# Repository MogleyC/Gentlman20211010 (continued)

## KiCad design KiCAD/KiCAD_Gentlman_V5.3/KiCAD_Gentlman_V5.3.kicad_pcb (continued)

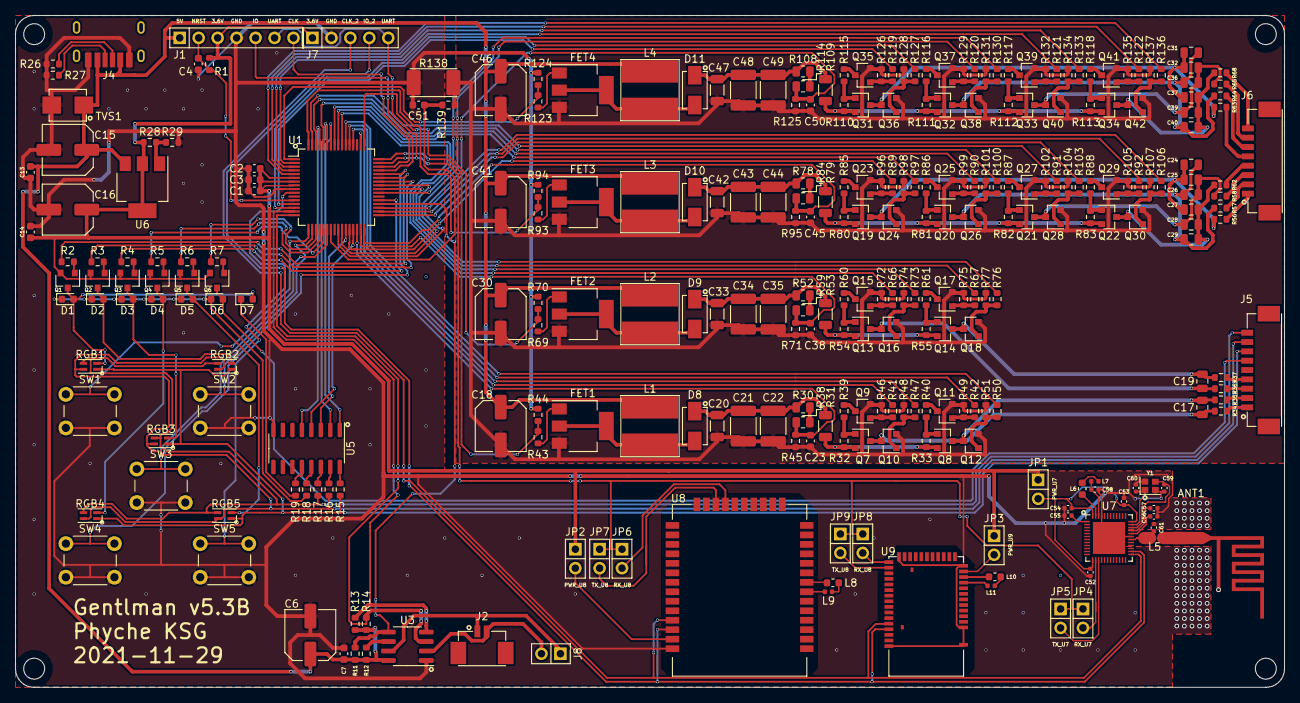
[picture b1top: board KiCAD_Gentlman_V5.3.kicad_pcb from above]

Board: 2 copper layers, 170.0 x 90.0 mm, 289 parts (0 on the bottom side), 207 nets.

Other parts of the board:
J1: PinHeader2.54mm_7; PinHeader_1x07_P2.54mm_Vertical
J2: 12505WR-02

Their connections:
+3.6V: J1.3; also elsewhere on the board
+5V: J1.1; also elsewhere on the board
/Main/NRST: J1.2; also elsewhere on the board
/Main/SWCLK: J1.7; also elsewhere on the board
/Main/SWDIO: J1.5; also elsewhere on the board
GNDPWR: J1.4; also elsewhere on the board
unnamed 80: J2.1; also elsewhere on the board
unnamed 81: J2.2; also elsewhere on the board
UART: J1.6; also elsewhere on the board

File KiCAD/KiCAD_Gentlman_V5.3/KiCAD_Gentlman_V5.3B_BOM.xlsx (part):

Reference | Quantity | Value | Footprint | Datasheet | Comment | Description | Field4 | MAKER | TYPE | Field5 | PartName | Shop
ANT1 | 1 | ANT | Custom:ANT_PATTERN | .\Dataseets\001-91445_AN91445_Antenna_Design_and_RF_Layout_Guidelines.pdf |  |  | PATTERN
C17 C19 C24 C25 C26 C27 C28 C29 C31 C32 C36 C37 C39 C40 | 14 | CAP_101K_250V_2012 | Custom:C_0805_2012Metric | ~ | CC0805JRNPOYBN101 | CHIP CERAMIC CAP | 101K/250V | YAGEO | 2012 |  |  | https://www.eleparts.co.kr/goods/view?no=9594793
C20 C33 C42 C47 | 4 | CAP_103K_250V_3216 | Custom:C_1206_3216Metric | .\Dataseets\TCC1206X7R103K251DT_10nF_250V_K.pdf | TCC1206X7R103K251DT | CHIP CERAMIC CAP | TCC1206X7R103K251DT | CCTC | 3216 |  |  | https://www.eleparts.co.kr/goods/view?no=8016042
C21 C22 C34 C35 C43 C44 C48 C49 | 8 | CAP_105K_250V_4532 | Custom:C_1812_4532Metric | .\Dataseets\FS43X105K251EGG_1uF_250V_K.pdf | FS43X105K251EGG | CHIP CERAMIC CAP | FS43X105K251EGG | WALSIN | 4532 |  |  | https://www.eleparts.co.kr/goods/view?no=8016951
C23 C38 C45 C50 C51 | 5 | CAP_103K_25V_1608 | Custom:C_0603_1608Metric | ~ | CC0603KRX7R8BB103 | CHIP CERAMIC CAP | 103K/25V | YAGEO | 1608 |  |  | https://www.eleparts.co.kr/goods/view?no=8057789#goodContent_3
C1 C2 C3 C4 C7 C13 C14 | 7 | CAP_104Z_25V_1608 | Custom:C_0603_1608Metric | ~ | CL10B104KA8NNNC | CHIP CERAMIC CAP | 104Z/25V | SAMSUNG ELECTRO-MECHANICS | 1608 |  |  | https://www.eleparts.co.kr/goods/view?no=8010066
C54 | 1 | CAP_4.7uF_1005 | Custom:C_0402_1005Metric | .\Dataseets\MLCC-1837944.pdf | CL05A475KP5NRNC | CHIP CERAMIC CAP | 4.7uF/짹10 | SAMSUNG ELECTRO-MECHANICS | 1005 |  | CL05A475KQ5NRNC | https://www.eleparts.co.kr/goods/view?no=8057798
C56 | 1 | CAP_N.C_1005 | Custom:C_0402_1005Metric | ~ | N.C | CHIP CERAMIC CAP | N.C | MURATA ELECTRONICS | 1005
C52 C53 C55 C57 | 4 | CAP_100nF_1005 | Custom:C_0402_1005Metric | .\Dataseets\GRM155R61H104KE14_01A-1983917.pdf | CL05A104KA5NNNC | CHIP CERAMIC CAP | 100nF/짹10 | SAMSUNG ELECTRO-MECHANICS | 1005 |  | GRM155R61H104KE14D | https://www.eleparts.co.kr/goods/view?no=8011439
C58 | 1 | CAP_1uF_1005 | Custom:C_0402_1005Metric | .\Dataseets\Samsung_MLCC_1837944-1929650.pdf | CL05A105KA5NQNC | CHIP CERAMIC CAP | 1uF/짹10 | SAMSUNG ELECTRO-MECHANICS | 1005 |  | CL05A105KP5NNWC | https://www.eleparts.co.kr/goods/view?no=8010445
C6 C15 C16 C18 C30 C41 C46 | 7 | CAP_220uF_6.3V_SC6.3X5.8 | Custom:C_Elec_6.3x5.8 | ~ | 220uF/6.3V | SMD ELECT CAPACITOR | 220uF/6.3V | SAMYOUNG | SC 6.3X5.8 | SC 6.3X5.8 |  | https://www.eleparts.co.kr/goods/view?no=3369557
C59 C60 | 2 | CAP_12pF_1005 | Custom:C_0402_1005Metric | .\Dataseets\GRM1555C1H120GA01_01A-1982688.pdf | 0402N120G250CT | CHIP CERAMIC CAP | 12pF/NP0/짹2 | WALSIN | 1005 |  | GRM1555C1H120GA01D | https://www.eleparts.co.kr/goods/view?no=9226620
C61 | 1 | CAP_0.8pF_1005 | Custom:C_0402_1005Metric | .\Dataseets\GRM1555C1HR80WA01_01A-1983059.pdf | GRM1555C1HR80WA01D | CHIP CERAMIC CAP | 0.8pF/NP0/짹5 | MURATA ELECTRONICS | 1005 |  | GRM1555C1HR80WA01D | https://www.eleparts.co.kr/goods/view?no=9591919
D1 D2 D3 D4 D5 D6 D7 | 7 | WR106SR-W | Custom:LED_0603_1608Metric | .\Dataseets\WR106SR-W.pdf | WR106SR-W | CHIP LED RED |  | BRIGHT LED | 1608 |  |  | https://www.eleparts.co.kr/goods/view?no=8104608
D8 D9 D10 D11 | 4 | MBRAF3200T3G | Custom:D_SMA | .\Dataseets\MBRAF3200T3_D-2315037.pdf | SS1200-LTP | SMD DIODE SCHOTTKY |  | Micro Commercial | SMA |  |  | https://www.eleparts.co.kr/goods/view?no=1799117
FET1 FET2 FET3 FET4 | 4 | FDT86246L | Custom:SOT-223-3_TabPin2 | .\Dataseets\FDT86246L-D.pdf | FDT86246L | SMD MOSFET N-CHANNEL |  | FAIRCHILD | SOT-223 |  |  | https://www.eleparts.co.kr/goods/view?no=6008399
J1 | 1 | PinHeader2.54mm_7 | Custom:PinHeader_1x07_P2.54mm_Vertical | ~ | PinHeader2.54mm-7P | PIN HEADER | DOWNLOAD | YEONHO ELECTRONICS | DIP-7
J2 | 1 | 12505WR-02 | Custom:12505WR-02 | .\Dataseets\12505-NN.pdf | 12505WR-02 | SMD WAFER | SPEAK1 | YEONHO ELECTRONICS | SMD-2 |  |  | https://www.devicemart.co.kr/goods/view?no=1381566
J4 | 1 | USB-TYPE-C-31-M-17 | Custom:TYPE-C-31-M-17-1 | .\Dataseets\Korean-Hroparts-Elec-TYPE-C-31-M-17.pdf | USB-TYPE-C-31-M-17 | SMD JACK USB C TYPE |  | Korean-Hroparts-Elec | SMD-6 |  |  | https://www.eleparts.co.kr/goods/view?no=7655653
J5 | 1 | 12505WS-09 | Custom:12505WS-09 | .\Dataseets\12505-NN.pdf | 12505WS-09 | SMD WAFER | CH1/CH2/RGB6 | YEONHO ELECTRONICS | SMD-9 |  |  | https://www.devicemart.co.kr/goods/view?no=12012614
J6 | 1 | 12505WS-08 | Custom:12505WS-08 | .\Dataseets\12505-NN.pdf | 12505WS-08 | SMD WAFER | CH3/CH4 | YEONHO ELECTRONICS | SMD-8 |  |  | https://www.devicemart.co.kr/goods/view?no=12012611
J7 | 1 | PinHeader2.54mm_5 | Custom:PinHeader_1x05_P2.54mm_Vertical | ~ | PinHeader2.54mm-5P | PIN HEADER |  |  | DIP-5
JP1 JP2 JP3 | 3 | PinHeader2.54mm-2-Jumper | Custom:PinHeader_1x02_P2.54mm_Vertical | ~ | PinHeader2.54mm-2P | PIN HEADER |  |  | DIP-2
L1 L2 L3 L4 | 4 | SC7850D-221K | Custom:L_SC7850D-221K | http://seokwangcoil.co.kr/7850 | SC7850D-221K | SMD INDUCTOR |  | SUHKWANG | 7850 |  |  | https://www.devicemart.co.kr/goods/view?no=6606
L5 | 1 | L_3.9nH | Custom:L_0402_1005Metric | .\Dataseets\7447840039G-2492425.pdf | LQG15HS3N9C02D | SMD INDUCTOR | 3.9nH/SHF6Ghz/짹5% | MURATA | 1005 |  | 7447840039G | https://www.eleparts.co.kr/goods/view?no=9578079
L6 L8 L10 | 3 | L_10uH | Custom:L_0603_1608Metric | .\Dataseets\JELF243B_0012-1633801.pdf | LQM18FN100M00D | SMD INDUCTOR | 10uH/50mA/짹20% | MURATA | 603 |  | LQM18FN100M00D | https://www.eleparts.co.kr/goods/view?no=7457243
L7 L9 L11 | 3 | L_15nH | Custom:L_0402_1005Metric | .\Dataseets\jti-cat-rf-ind-844822.pdf | LQG15HS15NJ02D | SMD INDUCTOR | 15nH/SHF2.45Ghz/짹10% | MURATA | 1005 |  | L-07C15NKV6T | https://www.eleparts.co.kr/goods/view?no=6591752
Q1 Q2 Q3 Q4 Q5 Q6 | 6 | MMBT200 | Custom:SOT-23 | .\Dataseets\AUKCS02423-1.pdf | MMBT200 | CHIP TRANSISTOR |  | ON SEMICONDUCTOR | SOT-23 |  |  | https://www.eleparts.co.kr/goods/view?no=7467326
Q7 Q8 Q13 Q14 Q19 Q20 Q21 Q22 Q31 Q32 Q33 Q34 | 12 | 2N5401S | Custom:SOT-23 | .\Dataseets\2N5401S.pdf | 2N5401S | CHIP TRANSISTOR |  | FIRST SILICON | SOT-23 |  |  | https://www.eleparts.co.kr/goods/view?no=6561296
Q9 Q10 Q11 Q12 Q15 Q16 Q17 Q18 Q23 Q24 Q25 Q26 Q27 Q28 Q29 Q30 Q35 Q36 Q37 Q38 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 | 24 | 2N5551S | Custom:SOT-23 | .\Dataseets\2N5550_1S_Ver2.pdf | 2N5551S | CHIP TRANSISTOR |  | FIRST SILICON | SOT-23 |  |  | https://www.eleparts.co.kr/goods/view?no=6561301
R1 | 1 | R_10KJ | Custom:R_0603_1608Metric | ~ | 10KJ | CHIP RESISTOR | 10KJ | WALSIN, SAMSUNG | 1608
R11 R12 R13 R14 R41 R42 R47 R50 R66 R67 R73 R76 R89 R90 R91 R92 R97 R100 R103 R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 | 29 | R_1KF | Custom:R_0603_1608Metric | ~ | 1KF | CHIP RESISTOR | 1KF | WALSIN, SAMSUNG | 1608 |  |  | https://www.devicemart.co.kr/goods/view?no=6058
R138 | 1 | R_0RJ_6432 | Custom:R_3522_6432Metric | ~ | 0RJ | CHIP RESISTOR | 0RJ | WALSIN, SAMSUNG | 6432 |  |  | https://www.devicemart.co.kr/goods/view?no=1089663
R15 R16 R17 R18 R19 | 5 | R_47RJ | Custom:R_0603_1608Metric | ~ | 47RJ | CHIP RESISTOR | 47RJ | WALSIN, SAMSUNG | 1608
R2 R3 R4 R5 R6 R7 | 6 | R_390RJ | Custom:R_0603_1608Metric | ~ | 390RJ | CHIP RESISTOR | 390RJ | WALSIN, SAMSUNG | 1608
R26 R27 | 2 | R_4.7KF | Custom:R_0603_1608Metric | ~ | 4.7KF | CHIP RESISTOR | 4.7KF | WALSIN, SAMSUNG | 1608
R28 | 1 | R_270RF | Custom:R_0603_1608Metric | ~ | 270RF | CHIP RESISTOR | 270RF | WALSIN, SAMSUNG | 1608
R29 | 1 | R_510RF | Custom:R_0603_1608Metric | ~ | 510RF | CHIP RESISTOR | 510RF | WALSIN, SAMSUNG | 1608
R30 R38 R52 R59 R78 R84 R108 R114 | 8 | R_150KF_2012 | Custom:R_0805_2012Metric | ~ | 150KF | CHIP RESISTOR | 150KF | WALSIN, SAMSUNG | 2012
R31 R53 R79 R109 | 4 | R_120RJ_3216 | Custom:R_1206_3216Metric | ~ | 120RJ | CHIP RESISTOR | 120RJ | WALSIN, SAMSUNG | 3216
R34 R35 R36 R37 R56 R57 R58 R62 R63 R64 R65 R68 | 12 | R_2.7KF | Custom:R_0603_1608Metric | ~ | 2.7KF | CHIP RESISTOR | 2.7KF | WALSIN, SAMSUNG | 1608
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
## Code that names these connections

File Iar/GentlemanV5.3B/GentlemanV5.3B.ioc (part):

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Mcu.Name=STM32G070RBTx
Mcu.Package=LQFP64
Mcu.UserName=STM32G070RBTx
PA0.GPIOParameters=GPIO_PuPd,GPIO_Label
PA0.GPIO_Label=SW1
PA0.GPIO_PuPd=GPIO_PULLUP
PA0.Signal=GPIO_Input
PA1.GPIOParameters=GPIO_PuPd,GPIO_Label
PA1.GPIO_Label=SW2
PA1.GPIO_PuPd=GPIO_PULLUP
PA1.Signal=GPIO_Input
PA10.GPIOParameters=PinState,GPIO_PuPd,GPIO_Label,GPIO_ModeDefaultOutputPP
PA10.GPIO_Label=LED_TR2
PA10.GPIO_ModeDefaultOutputPP=GPIO_MODE_OUTPUT_OD
PA10.GPIO_PuPd=GPIO_PULLUP
PA10.PinState=GPIO_PIN_SET
PA10.Signal=GPIO_Output
PA11\ [PA9].GPIOParameters=PinState,GPIO_PuPd,GPIO_Label,GPIO_ModeDefaultOutputPP
PA11\ [PA9].GPIO_Label=LED_TR1
PA11\ [PA9].GPIO_ModeDefaultOutputPP=GPIO_MODE_OUTPUT_OD
PA11\ [PA9].GPIO_PuPd=GPIO_PULLUP
PA11\ [PA9].PinState=GPIO_PIN_SET
PA11\ [PA9].Signal=GPIO_Output
PA12\ [PA10].GPIOParameters=GPIO_PuPd,GPIO_Label
PA12\ [PA10].GPIO_Label=SW4
PA12\ [PA10].GPIO_PuPd=GPIO_PULLUP
PA12\ [PA10].Signal=GPIO_Input
PA13.Mode=Serial_Wire
PA13.Signal=SYS_SWDIO
PA14-BOOT0.Mode=Serial_Wire
PA14-BOOT0.Signal=SYS_SWCLK
PA15.GPIOParameters=GPIO_ModeDefaultPP,GPIO_PuPd,GPIO_Label
PA15.GPIO_Label=UART2
PA15.GPIO_ModeDefaultPP=GPIO_MODE_AF_OD
PA15.GPIO_PuPd=GPIO_PULLUP
PA15.Signal=USART2_RX
PA2.GPIOParameters=PinState,GPIO_PuPd,GPIO_Label,GPIO_ModeDefaultOutputPP
PA2.GPIO_Label=LED_TR6
PA2.GPIO_ModeDefaultOutputPP=GPIO_MODE_OUTPUT_OD
PA2.GPIO_PuPd=GPIO_PULLUP
PA2.PinState=GPIO_PIN_SET
PA2.Signal=GPIO_Output
PA3.GPIOParameters=PinState,GPIO_PuPd,GPIO_Label,GPIO_ModeDefaultOutputPP
PA3.GPIO_Label=LED_TR5
PA3.GPIO_ModeDefaultOutputPP=GPIO_MODE_OUTPUT_OD
PA3.GPIO_PuPd=GPIO_PULLUP
PA3.PinState=GPIO_PIN_SET
PA3.Signal=GPIO_Output
PA4.GPIOParameters=PinState,GPIO_PuPd,GPIO_Label,GPIO_ModeDefaultOutputPP
PA4.GPIO_Label=LED_TR4
PA4.GPIO_ModeDefaultOutputPP=GPIO_MODE_OUTPUT_OD
PA4.GPIO_PuPd=GPIO_PULLUP
PA4.PinState=GPIO_PIN_SET
PA4.Signal=GPIO_Output
PA5.GPIOParameters=GPIO_PuPd,GPIO_Label
PA5.GPIO_Label=SW3
PA5.GPIO_PuPd=GPIO_PULLUP
PA5.Signal=GPIO_Input
PA6.GPIOParameters=GPIO_Label
PA6.GPIO_Label=ADC_CURR
PA6.Mode=IN6
PA6.Signal=ADC1_IN6
PA7.GPIOParameters=GPIO_PuPd,GPIO_Label
PA7.GPIO_Label=SOUND2_IN
PA7.GPIO_PuPd=GPIO_PULLDOWN
PA7.Signal=GPIO_Output
PA8.GPIOParameters=GPIO_Speed,PinState,GPIO_PuPd,GPIO_Label,GPIO_ModeDefaultOutputPP
PA8.GPIO_Label=SOUND1_EN
PA8.GPIO_ModeDefaultOutputPP=GPIO_MODE_OUTPUT_OD
PA8.GPIO_PuPd=GPIO_PULLUP
PA8.GPIO_Speed=GPIO_SPEED_FREQ_LOW
PA8.PinState=GPIO_PIN_SET
PA8.Signal=GPIO_Output
PA9.GPIOParameters=PinState,GPIO_PuPd,GPIO_Label,GPIO_ModeDefaultOutputPP
PA9.GPIO_Label=LED_TR3
PA9.GPIO_ModeDefaultOutputPP=GPIO_MODE_OUTPUT_OD
PA9.GPIO_PuPd=GPIO_PULLUP
PA9.PinState=GPIO_PIN_SET
PA9.Signal=GPIO_Output
PB0.GPIOParameters=GPIO_PuPd,GPIO_Label
PB0.GPIO_Label=LED_DTR3
PB0.GPIO_PuPd=GPIO_PULLDOWN
PB0.Signal=GPIO_Output
PB1.GPIOParameters=GPIO_PuPd,GPIO_Label
PB1.GPIO_Label=CH3_1_1
PB1.GPIO_PuPd=GPIO_PULLDOWN
PB1.Signal=GPIO_Output
PB10.GPIOParameters=GPIO_Label
PB10.GPIO_Label=ADC_CH1
PB10.Mode=IN11
PB10.Signal=ADC1_IN11
PB11.GPIOParameters=GPIO_Label
PB11.GPIO_Label=ADC_CH2
PB11.Mode=IN15
PB11.Signal=ADC1_IN15
PB12.GPIOParameters=GPIO_Label
PB12.GPIO_Label=ADC_CH3
PB12.Mode=IN16
PB12.Signal=ADC1_IN16
PB13.GPIOParameters=GPIO_PuPd,GPIO_Label
PB13.GPIO_Label=CH3_3_2
PB13.GPIO_PuPd=GPIO_PULLDOWN
PB13.Signal=GPIO_Output
PB14.GPIOParameters=GPIO_PuPd,GPIO_Label
PB14.GPIO_Label=CH3_4_1
PB14.GPIO_PuPd=GPIO_PULLDOWN
PB14.Signal=GPIO_Output
PB15.GPIOParameters=GPIO_PuPd,GPIO_Label
PB15.GPIO_Label=CH3_4_2
PB15.GPIO_PuPd=GPIO_PULLDOWN
PB15.Signal=GPIO_Output
PB2.GPIOParameters=GPIO_PuPd,GPIO_Label
PB2.GPIO_Label=LED_DTR4
PB2.GPIO_PuPd=GPIO_PULLDOWN
PB2.Signal=GPIO_Output
PB3.GPIOParameters=GPIO_PuPd,GPIO_Label
PB3.GPIO_Label=CH3_1_2
PB3.GPIO_PuPd=GPIO_PULLDOWN
PB3.Signal=GPIO_Output
PB4.GPIOParameters=GPIO_PuPd,GPIO_Label
PB4.GPIO_Label=LED_DTR1
PB4.GPIO_PuPd=GPIO_PULLDOWN
PB4.Signal=GPIO_Output
PB5.GPIOParameters=GPIO_PuPd,GPIO_Label
PB5.GPIO_Label=LED_DTR2
PB5.GPIO_PuPd=GPIO_PULLDOWN
PB5.Signal=GPIO_Output
PB6.GPIOParameters=GPIO_PuPd,GPIO_Label
PB6.GPIO_Label=CH3_2_1
PB6.GPIO_PuPd=GPIO_PULLDOWN
PB6.Signal=GPIO_Output
PB7.GPIOParameters=GPIO_PuPd,GPIO_Label
PB7.GPIO_Label=LED_DTR5
PB7.GPIO_PuPd=GPIO_PULLDOWN
PB7.Signal=GPIO_Output
PB8.GPIOParameters=GPIO_PuPd,GPIO_Label
PB8.GPIO_Label=CH3_2_2
PB8.GPIO_PuPd=GPIO_PULLDOWN
PB8.Signal=GPIO_Output
PB9.GPIOParameters=GPIO_PuPd,GPIO_Label
PB9.GPIO_Label=CH3_3_1
PB9.GPIO_PuPd=GPIO_PULLDOWN
PB9.Signal=GPIO_Output
PC0.GPIOParameters=GPIO_PuPd,GPIO_Label
PC0.GPIO_Label=CH4_1_1
PC0.GPIO_PuPd=GPIO_PULLDOWN
PC0.Signal=GPIO_Output
PC1.GPIOParameters=GPIO_PuPd,GPIO_Label
PC1.GPIO_Label=CH4_1_2
PC1.GPIO_PuPd=GPIO_PULLDOWN
PC1.Signal=GPIO_Output
PC10.GPIOParameters=GPIO_Speed,GPIO_PuPd,GPIO_Label
PC10.GPIO_Label=CTL_CH3
PC10.GPIO_PuPd=GPIO_PULLDOWN
PC10.GPIO_Speed=GPIO_SPEED_FREQ_LOW
PC10.Signal=S_TIM1_CH3
PC11.GPIOParameters=GPIO_PuPd,GPIO_Label
PC11.GPIO_Label=CTL_CH4
PC11.GPIO_PuPd=GPIO_PULLDOWN
PC11.Signal=S_TIM1_CH4
PC12.GPIOParameters=GPIO_PuPd,GPIO_Label
PC12.GPIO_Label=CH4_3_1
PC12.GPIO_PuPd=GPIO_PULLDOWN
PC12.Signal=GPIO_Output
PC13.GPIOParameters=GPIO_PuPd,GPIO_Label
PC13.GPIO_Label=CH4_3_2
PC13.GPIO_PuPd=GPIO_PULLDOWN
PC13.Signal=GPIO_Output
PC14-OSC32_IN\ (PC14).GPIOParameters=GPIO_PuPd,GPIO_Label
PC14-OSC32_IN\ (PC14).GPIO_Label=CH4_4_1
PC14-OSC32_IN\ (PC14).GPIO_PuPd=GPIO_PULLDOWN
PC14-OSC32_IN\ (PC14).Signal=GPIO_Output
PC15-OSC32_OUT\ (PC15).GPIOParameters=GPIO_PuPd,GPIO_Label
PC15-OSC32_OUT\ (PC15).GPIO_Label=CH4_4_2
PC15-OSC32_OUT\ (PC15).GPIO_PuPd=GPIO_PULLDOWN
PC15-OSC32_OUT\ (PC15).Signal=GPIO_Output
PC2.GPIOParameters=GPIO_Speed,PinState,GPIO_PuPd,GPIO_Label,GPIO_ModeDefaultOutputPP
PC2.GPIO_Label=SOUND1_DATA
PC2.GPIO_ModeDefaultOutputPP=GPIO_MODE_OUTPUT_OD
PC2.GPIO_PuPd=GPIO_PULLUP
PC2.GPIO_Speed=GPIO_SPEED_FREQ_LOW
PC2.PinState=GPIO_PIN_RESET
PC2.Signal=GPIO_Output
PC3.GPIOParameters=GPIO_Speed,PinState,GPIO_PuPd,GPIO_Label,GPIO_ModeDefaultOutputPP
PC3.GPIO_Label=SOUND1_CLK
PC3.GPIO_ModeDefaultOutputPP=GPIO_MODE_OUTPUT_OD
PC3.GPIO_PuPd=GPIO_PULLUP
PC3.GPIO_Speed=GPIO_SPEED_FREQ_LOW
PC3.PinState=GPIO_PIN_SET
PC3.Signal=GPIO_Output
PC4.GPIOParameters=GPIO_Label
PC4.GPIO_Label=ADC_CH4
PC4.Mode=IN17
PC4.Signal=ADC1_IN17
PC5.GPIOParameters=GPIO_PuPd,GPIO_Label
PC5.GPIO_Label=CH4_2_1
PC5.GPIO_PuPd=GPIO_PULLDOWN
PC5.Signal=GPIO_Output
PC6.GPIOParameters=GPIO_PuPd,GPIO_Label
PC6.GPIO_Label=SOUND2_SD
PC6.GPIO_PuPd=GPIO_PULLDOWN
PC6.Signal=GPIO_Output
PC7.GPIOParameters=GPIO_PuPd,GPIO_Label
PC7.GPIO_Label=CH4_2_2
PC7.GPIO_PuPd=GPIO_PULLDOWN
PC7.Signal=GPIO_Output
PC8.GPIOParameters=GPIO_PuPd,GPIO_Label
PC8.GPIO_Label=CTL_CH1
PC8.GPIO_PuPd=GPIO_PULLDOWN
PC8.Signal=S_TIM1_CH1
PC9.GPIOParameters=GPIO_PuPd,GPIO_Label
PC9.GPIO_Label=CTL_CH2
PC9.GPIO_PuPd=GPIO_PULLDOWN
PC9.Signal=S_TIM1_CH2
PD0.GPIOParameters=GPIO_PuPd,GPIO_Label
PD0.GPIO_Label=CH1_1_1
PD0.GPIO_PuPd=GPIO_PULLDOWN
PD0.Signal=GPIO_Output
PD1.GPIOParameters=GPIO_PuPd,GPIO_Label
PD1.GPIO_Label=FLASH_CLK
PD1.GPIO_PuPd=GPIO_PULLDOWN
PD1.Signal=GPIO_Output
PD2.GPIOParameters=GPIO_PuPd,GPIO_Label
PD2.GPIO_Label=CH1_1_2
PD2.GPIO_PuPd=GPIO_PULLDOWN
PD2.Signal=GPIO_Output
PD3.GPIOParameters=GPIO_PuPd,GPIO_Label
PD3.GPIO_Label=CH1_2_1
PD3.GPIO_PuPd=GPIO_PULLDOWN
PD3.Signal=GPIO_Output
PD4.GPIOParameters=GPIO_PuPd,GPIO_Label
PD4.GPIO_Label=CH1_2_2
PD4.GPIO_PuPd=GPIO_PULLDOWN
PD4.Signal=GPIO_Output
PD5.GPIOParameters=GPIO_PuPd,GPIO_Label
PD5.GPIO_Label=CH2_1_1
PD5.GPIO_PuPd=GPIO_PULLDOWN
PD5.Signal=GPIO_Output
PD6.GPIOParameters=GPIO_PuPd,GPIO_Label
PD6.GPIO_Label=CH2_1_2
PD6.GPIO_PuPd=GPIO_PULLDOWN
PD6.Signal=GPIO_Output
PD8.GPIOParameters=GPIO_PuPd,GPIO_Label
PD8.GPIO_Label=CH2_2_1
PD8.GPIO_PuPd=GPIO_PULLDOWN
PD8.Signal=GPIO_Output
PD9.GPIOParameters=GPIO_PuPd,GPIO_Label
PD9.GPIO_Label=CH2_2_2
PD9.GPIO_PuPd=GPIO_PULLDOWN
PD9.Signal=GPIO_Output
PF0-OSC_IN\ (PF0).GPIOParameters=GPIO_PuPd,GPIO_Label
PF0-OSC_IN\ (PF0).GPIO_Label=SW5
PF0-OSC_IN\ (PF0).GPIO_PuPd=GPIO_PULLUP
PF0-OSC_IN\ (PF0).Signal=GPIO_Input
RCC.HSE_VALUE=8000000
RCC.SYSCLKFreq_VALUE=64000000
RCC.SYSCLKSource=RCC_SYSCLKSOURCE_PLLCLK
board=custom

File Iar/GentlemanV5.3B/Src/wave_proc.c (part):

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//#define CH4_CH4_1_Flag 0x80
//#define CH4_CH4_2_Flag 0x40

#define CH1_P1_CTL1	RunTblBuf.CH1H1
#define CH1_P1_CTL2	RunTblBuf.CH1L1
#define CH1_P2_CTL1	RunTblBuf.CH1H2
#define CH1_P2_CTL2	RunTblBuf.CH1L2

#define CH2_P1_CTL1	RunTblBuf.CH2H1
#define CH2_P1_CTL2	RunTblBuf.CH2L1
#define CH2_P2_CTL1	RunTblBuf.CH2H2
#define CH2_P2_CTL2	RunTblBuf.CH2L2

#define CH3_P1_CTL1	RunTblBuf.CH3H1
#define CH3_P1_CTL2	RunTblBuf.CH3L1
#define CH3_P2_CTL1	RunTblBuf.CH3H2
#define CH3_P2_CTL2	RunTblBuf.CH3L2
#define CH3_P3_CTL1	RunTblBuf.CH3H3
#define CH3_P3_CTL2	RunTblBuf.CH3L3
#define CH3_P4_CTL1	RunTblBuf.CH3H4
#define CH3_P4_CTL2	RunTblBuf.CH3L4

#define CH4_P1_CTL1	RunTblBuf.CH4H1
#define CH4_P1_CTL2	RunTblBuf.CH4L1
#define CH4_P2_CTL1	RunTblBuf.CH4H2
#define CH4_P2_CTL2	RunTblBuf.CH4L2
#define CH4_P3_CTL1	RunTblBuf.CH4H3
#define CH4_P3_CTL2	RunTblBuf.CH4L3
#define CH4_P4_CTL1	RunTblBuf.CH4H4
#define CH4_P4_CTL2	RunTblBuf.CH4L4

#define PT_Freq_Step_Change 10

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	case 1:
	{
		//Ch_1 Low & Discharge
		CH1_P1_CTL2 = 0;
		CH1_P2_CTL2 = 0;

		//Ch_1_1
		if (CH1_P1_CTL1 == 1)
		{
			CH1_P1_CTL1 = 0;
			CH1_P1_CTL2 = 1;
		}

		//Ch_1_2
		if (CH1_P2_CTL1 == 1)
		{
			CH1_P2_CTL1 = 0;
			CH1_P2_CTL2 = 1;
		}

		break;	//switch exit
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	case 2:
	{
		//Ch_2 Low & Discharge
		CH2_P1_CTL2 = 0;
		CH2_P2_CTL2 = 0;

		//Ch_1_1
		if (CH2_P1_CTL1 == 1)
		{
			CH2_P1_CTL1 = 0;
			CH2_P1_CTL2 = 1;
		}

		//Ch_1_2
		if (CH2_P2_CTL1 == 1)
		{
			CH2_P2_CTL1 = 0;
			CH2_P2_CTL2 = 1;
		}

		break;	//switch exit
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	case 3:
	{
		//Ch_3 Low & Discharge
		CH3_P1_CTL2 = 0;
		CH3_P2_CTL2 = 0;
		CH3_P3_CTL2 = 0;
		CH3_P4_CTL2 = 0;

		//Ch_3_1
		if (CH3_P1_CTL1 == 1)
		{
			CH3_P1_CTL1 = 0;
			CH3_P1_CTL2 = 1;
		}

		//Ch_3_2
		if (CH3_P2_CTL1 == 1)
		{
			CH3_P2_CTL1 = 0;
			CH3_P2_CTL2 = 1;
		}

		//Ch_3_3
		if (CH3_P3_CTL1 == 1)
		{
			CH3_P3_CTL1 = 0;
			CH3_P3_CTL2 = 1;
		}

		//Ch_3_4
		if (CH3_P4_CTL1 == 1)
		{
			CH3_P4_CTL1 = 0;
			CH3_P4_CTL2 = 1;
		}

		break;	//switch exit
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	case 4:
	{
		//Ch_4 Low & Discharge
		CH4_P1_CTL2 = 0;
		CH4_P2_CTL2 = 0;
		CH4_P3_CTL2 = 0;
		CH4_P4_CTL2 = 0;

		//Ch_4_1
		if (CH4_P1_CTL1 == 1)
		{
			CH4_P1_CTL1 = 0;
			CH4_P1_CTL2 = 1;
		}

		//Ch_4_2
		if (CH4_P2_CTL1 == 1)
		{
			CH4_P2_CTL1 = 0;
			CH4_P2_CTL2 = 1;
		}

		//Ch_4_3
		if (CH4_P3_CTL1 == 1)
		{
			CH4_P3_CTL1 = 0;
			CH4_P3_CTL2 = 1;
		}

		//Ch_4_4
		if (CH4_P4_CTL1 == 1)
		{
			CH4_P4_CTL1 = 0;
			CH4_P4_CTL2 = 1;
		}

		break;	//switch exit
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				tmpPinSetValue = Pattern_Base[PT_Freq_CategoryID[0]][PT_Freq_ID];
				if ((tmpPinSetValue & CH1_PD1_Flag) != 0x00)
				{
					CH1_P1_CTL1 = 1;
					CH1_P2_CTL2 = 1;
				}
				else if ((tmpPinSetValue & CH1_PD2_Flag) != 0x00)
				{
					CH1_P2_CTL1 = 1;
					CH1_P1_CTL2 = 1;
				}

				++PT_Freq_Step;
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				tmpPinSetValue = Pattern_Base[PT_Freq_CategoryID[1]][PT_Freq_ID];
				if ((tmpPinSetValue & CH2_PD1_Flag) != 0x00)
				{
					CH2_P1_CTL1 = 1;
					CH2_P2_CTL2 = 1;
				}
				else if ((tmpPinSetValue & CH2_PD2_Flag) != 0x00)
				{
					CH2_P2_CTL1 = 1;
					CH2_P1_CTL2 = 1;
				}

				++PT_Freq_Step;
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				//Ch_3_1
				if ((tmpPinSetValue & CH3_CH1_1_Flag) != 0x00)
				{
					CH3_P1_CTL1 = 1;
				}
				else if ((tmpPinSetValue & CH3_CH1_2_Flag) != 0x00)
				{
					CH3_P1_CTL2 = 1;
				}

				//Ch_3_2
				if ((tmpPinSetValue & CH3_CH2_1_Flag) != 0x00)
				{
					CH3_P2_CTL1 = 1;
				}
				else if ((tmpPinSetValue & CH3_CH2_2_Flag) != 0x00)
				{
					CH3_P2_CTL2 = 1;
				}

				//Ch_3_3
				if ((tmpPinSetValue & CH3_CH3_1_Flag) != 0x00)
				{
					CH3_P3_CTL1 = 1;
				}
				else if ((tmpPinSetValue & CH3_CH3_2_Flag) != 0x00)
				{
					CH3_P3_CTL2 = 1;
				}

				//Ch_3_4
				if ((tmpPinSetValue & CH3_CH4_1_Flag) != 0x00)
				{
					CH3_P4_CTL1 = 1;
				}
				else if ((tmpPinSetValue & CH3_CH4_2_Flag) != 0x00)
				{
					CH3_P4_CTL2 = 1;
				}

				++PT_Freq_Step;
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				//Ch_4_1
				if ((tmpPinSetValue & CH4_CH1_1_Flag) != 0x00)
				{
					CH4_P1_CTL1 = 1;
				}
				else if ((tmpPinSetValue & CH4_CH1_2_Flag) != 0x00)
				{
					CH4_P1_CTL2 = 1;
				}

				//Ch_4_2
				if ((tmpPinSetValue & CH4_CH2_1_Flag) != 0x00)
				{
					CH4_P2_CTL1 = 1;
				}
				else if ((tmpPinSetValue & CH4_CH2_2_Flag) != 0x00)
				{
					CH4_P2_CTL2 = 1;
				}

				//Ch_4_3
				if ((tmpPinSetValue & CH4_CH3_1_Flag) != 0x00)
				{
					CH4_P3_CTL1 = 1;
				}
				else if ((tmpPinSetValue & CH4_CH3_2_Flag) != 0x00)
				{
					CH4_P3_CTL2 = 1;
				}

				//Ch_4_4
				if ((tmpPinSetValue & CH4_CH4_1_Flag) != 0x00)
				{
					CH4_P4_CTL1 = 1;
				}
				else if ((tmpPinSetValue & CH4_CH4_2_Flag) != 0x00)
				{
					CH4_P4_CTL2 = 1;
				}

				++PT_Freq_Step;
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
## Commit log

2021-10-10 KSG : 라이선스 및 리드미 파일 제작
2021-10-10 KSG : KiCad프로젝트 생성 및 무시규칙, 유틸리티 업데이트
2021-10-18 KSG : 블루투스 모듈 데이터시트 업로드
2021-10-18 KSG : 잘못된 이름의 파일 제거
2021-10-18 KSG : KICAD 연습(G070RB 심볼 및 풋프린트 얹기)
2021-10-19 KSG : 일부파일 폴더 위치 변경
2021-10-19 KSG : KICAD 라이브러리 대량 업데이트 및 회로도 제작 연습
2021-10-20 KSG : 뉴클레오 UART 블루투스 통신 테스트 완료(휴대폰과 통신)
2021-10-28 KSG : 블루투스 모듈 오리지널 Hex파일 백업
2021-10-29 KSG : nRF5_SDK 업로드
2021-10-29 KSG : 커스텀 프로젝트 제작(GPIO, Dealy 구현 및 테스트)
2021-10-29 KSG : GPIOE 코드 구현
2021-10-29 KSG : doxy파일 구성 및 example ignore 구성
2021-10-29 KSG : Ses 셋팅 최적화 및 설정파일저장, 소스파일 최적화
2021-10-29 KSG : systick_delay적용 및 sdk_config wizard 설정
2021-10-30 KSG : 시스템틱 미싱코드 추가 및 클락 시스템 제어 코드 테스트
2021-10-30 KSG : 핀번호 관리 헤더 추가 및 LED 2개로 내용 수정
2021-10-31 KSG : UART 테스트 완료(Config중 UART_LEGACY 설정에 문제가 있음 확인 예정)
2021-10-31 KSG : UART 구축 완료
2021-11-02 KSG : sdk_config에서 clock설정이 잘못되어 있는 부분 수정. 또한 일부 오타수정 및 정렬 진행.
2021-11-02 KSG : 보드 핀번호 변경 및 기존 모듈 기능 최적화 및 라인정렬
2021-11-02 KSG : UART 최적화(UART 비연결시에도 동작되도록 작동)
2021-11-02 KSG : RSSI 테스트 완료
2021-11-02 KSG : 라디오 모듈 제작 및 테스트 완료
2021-11-05 KSG : NRF로그 시스템 추가, flash_placement수정, 소프트디바이스 적용
2021-11-06 KSG : SES 셋팅 설정 백업
2021-11-06 KSG : 셋팅 깨끗하게 하여 최적화
2021-11-06 KSG : SES 라이선스 추가
2021-11-06 KSG : 셋팅 최적화. 불필요 구문 삭제. 빌드시 내역 표시 기능 설정.
2021-11-06 KSG : BLE_UART 동작 코드 완료. 테스트 완료.(최적화 필요)
2021-11-13 KSG : V5.3 회로도 초본 완성(검토 필요) 일부 부품 데이터시트 추가
2021-11-18 KSG : V5.3 회로도 완성, 심볼 정보 업데이트 완료(데이터시트 및 풋프린트 등), 기존 BOM과 일치 완료
2021-11-18 KSG : 블루투스 회로도 작성 완료 (풋프린트 및 데이터시트 업데이트 완료)
2021-11-19 KSG : 반이중통신용 회로도 구성 완료
2021-11-23 KSG : 회로도 에 nRF52 DC-DC 레귤레이터 추가
2021-12-02 KSG : V5.3B용으로 회로도 수정 및 PCB 아트웤 완료.(샘플PCB주문됨)
2021-12-17 KSG : LM1117 데이터 시트 업데이트
2021-12-17 KSG : 테스트용 V5.3B IAR 펌웨어 소스 업로드(V5.2G기반 베이스)
2021-12-18 KSG : 보드 수정(크리스탈 배치 문제, 점퍼추가, 이름위치오기수정, IC1번핀표시)
2021-12-18 KSG : G5.3B_nRF 프로젝트 생성 및 nRF52832 클린 프로젝트 생성
2021-12-19 KSG : nRF52832 UART_BLE 동작버전 업로드
2021-12-19 KSG : nRF52810 프로젝트 생성 및 동작 확인.
2021-12-20 KSG : 간단 BLE 리모트용 프로토콜 제작 및 테스트 완료
2021-12-28 KSG : 안드로이드 스튜디오용 ignore 설정
2021-12-28 KSG : Serial Bluetooth Terminal 분석 및 업로드
2021-12-28 KSG : 버튼 아이콘 제작
2021-12-28 KSG : 버튼 다운시 레벨 0이 설정되는 버그 수정
2021-12-28 KSG : 안드로이드 이름 및 아이콘 변경. 프시케 전용 디바이스만 검색할 수 있도록 필터 적용.
2021-12-30 KSG : 리모트 시스템 및 로그 메일 전송 시스템 완성(테스트완료) 프로토콜 버전 수정
